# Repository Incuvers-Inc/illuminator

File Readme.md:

# Illuminator
LED Matrix illuminator for IRIS. Because, as any photographer will say, "good lighting is always needed to take a good picture."

## Hardware
- resistor network (one resistor per LED, 256 in total)
- 32x 74HC595 (for 256 outputs total)
- a dimming transistor for the fluorescence LED (5V PWM)
- a trigger transistor for the fluorescence LED (3.3V logic)
- a logic level shifter (four 3.3V -> 5V)
- capacitors to reduce kicks in current draw

### Power
The main power source will be used for the both illumination modules (matrix+ fluorescence LED). This can potentially blow the fuse is all of the components happen to be active at the same time. Luckily there is no requirement for them to simultaneously be active. The lighting flash is much shorter than the timescales for the environmental controls, so the latter can be disabled for the duration of the lighting flash. This must however be controlled by the software. Failure to account for this may result in a blown fuse.

### LED matrix
The fluorescence LED must first be disabled before the matrix LED is activated.

The LED matrix is driven by `74HC595` shift registers that can holds the state of up to 8 LEDs. The state of all the LED's must be first set before they are globally activated by grounding their shared `output_enable` pin.

#### Dimming
Global dimming is made possible with PWM on the `output_enable` input of the `74HC595`. All only one PWM signal is needed to dim the full matrix.

### Fluorescence LED
All the matrix LEDs must first be disabled before the fluorescence LED is lit.
The on/off state of the fluorescence LED is set from a single transistor.

#### Dimming
Dimming for the fluorescence LED is accomplished using the same PWM signal. In order for the matrix to stay off when the fluorescence LED is enabled, all the individual matrix LEDs must first be disabled.

### RPi interface
The RPi supplies inputs as the common PWM, fluorescence LED trigger, SPI for the matrix (three inputs) and of course a common ground.

Since the matrix is powered at 5V, the logic level (SPI and PWM) has to also be  shifted to 5V.

Since the fluorescence LED is trigger from a transistor, the logic level can stay at 3.3V.

## Software

### Illumination flash

The software must make sure that all the matrix LEDs are set to an `off` state after a pattern is finished flashing.
Iy may be good measure to be redundant and also do this before turning on the fluorescence LED.
The same goes for turning off the fluorescence LED before turning on the matrix.

### Power management

Since the LED's are powered from the main power source,
it is important to limit the total current draw from activated sub-components.
It is the software's responsibility to temporary disable components (heating/fans/valves) that could draw current for the duration of the illumination flash. Since this is rather short, it should cause any environmental noticeable disruptions.

NOTE: the activated camera sensor (and post processing) will also cause a short-lived increase in power demand, consider reactivating the environmental subcomponents only after the image is processed.

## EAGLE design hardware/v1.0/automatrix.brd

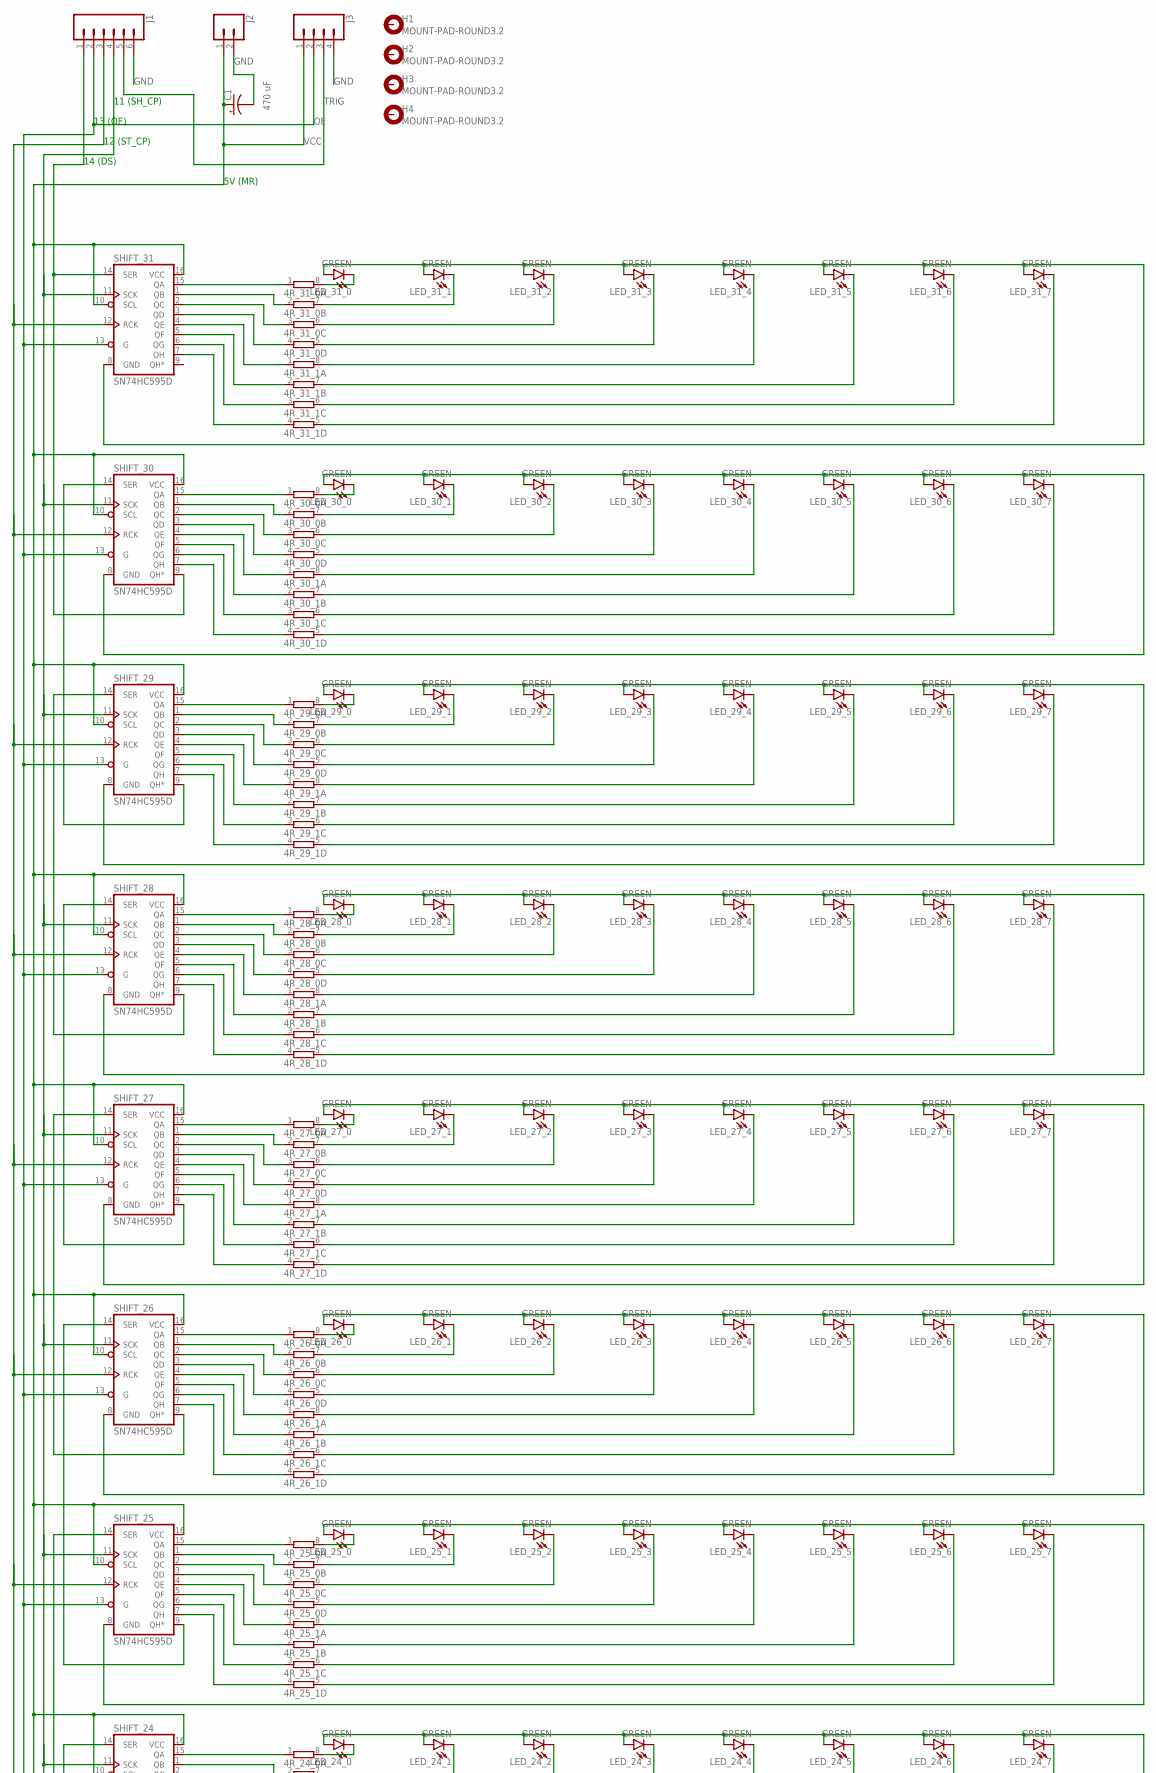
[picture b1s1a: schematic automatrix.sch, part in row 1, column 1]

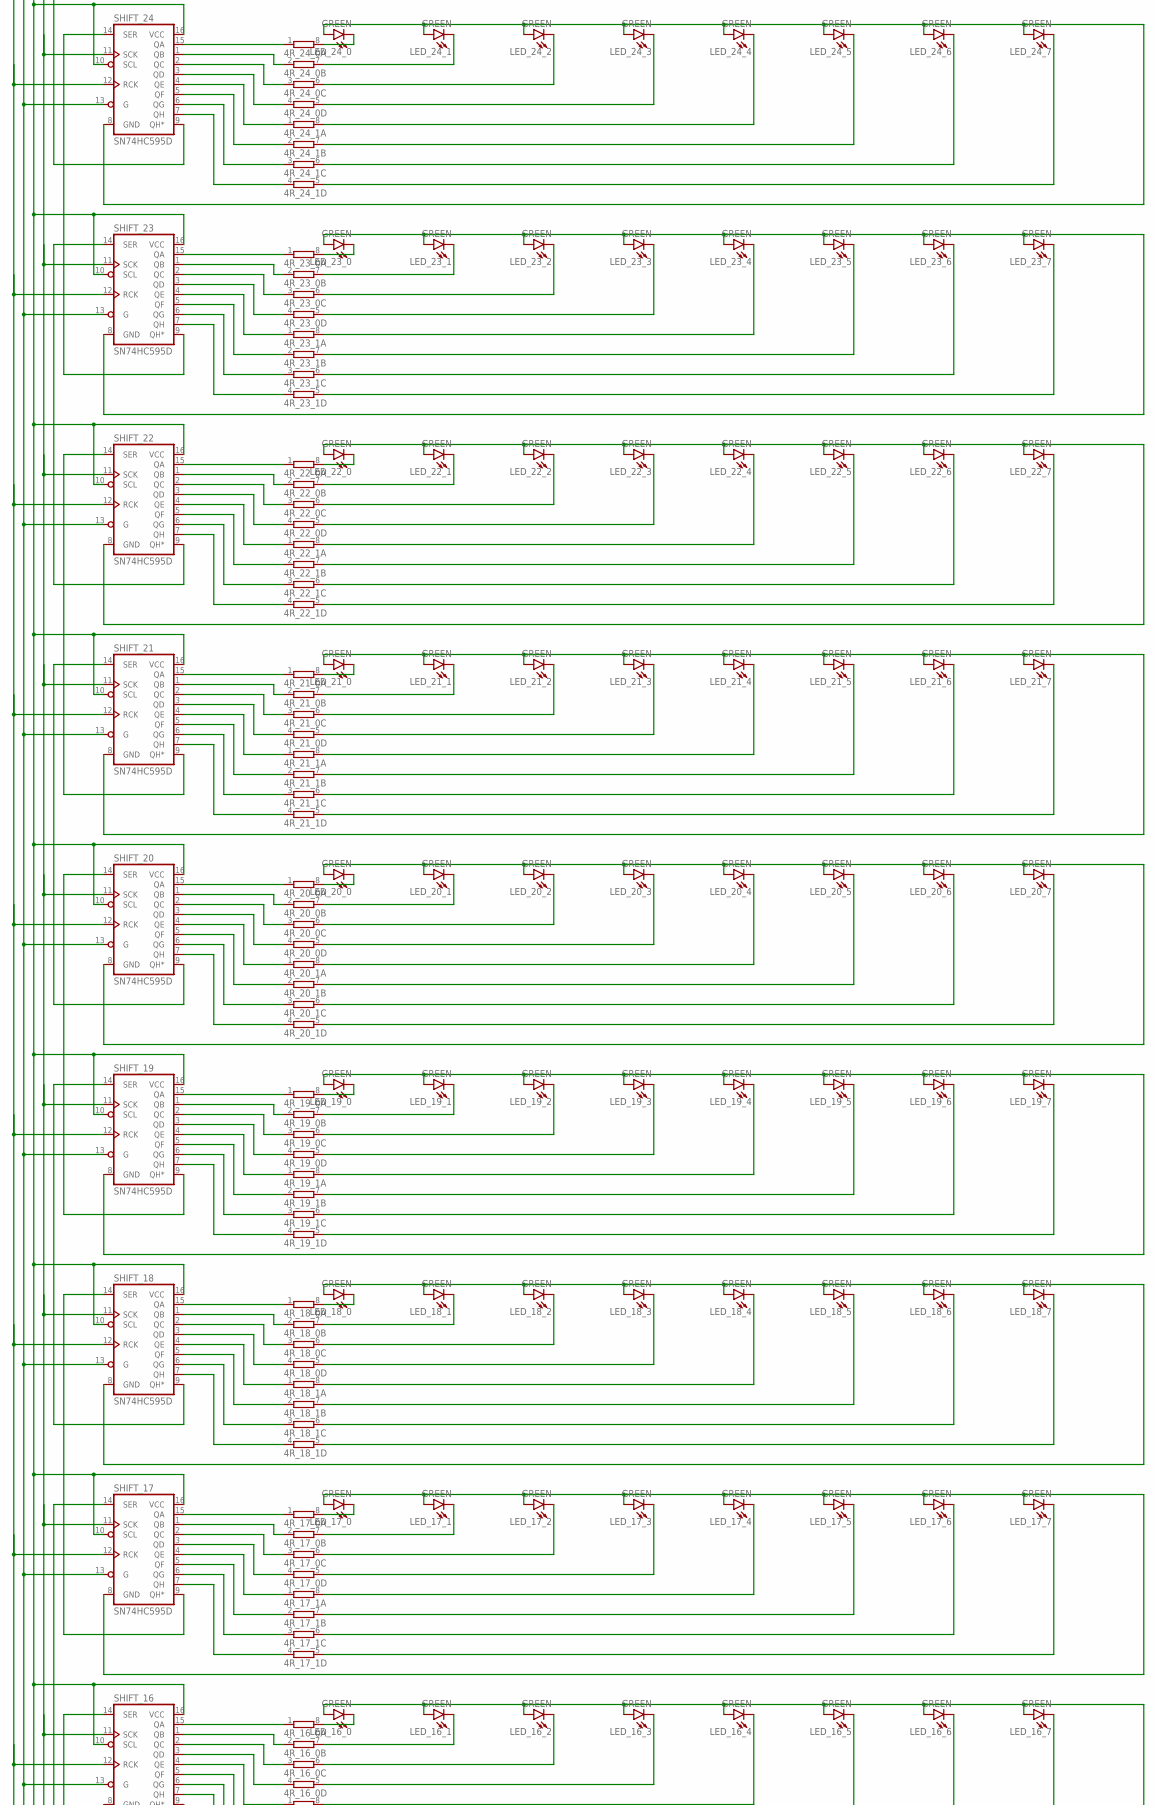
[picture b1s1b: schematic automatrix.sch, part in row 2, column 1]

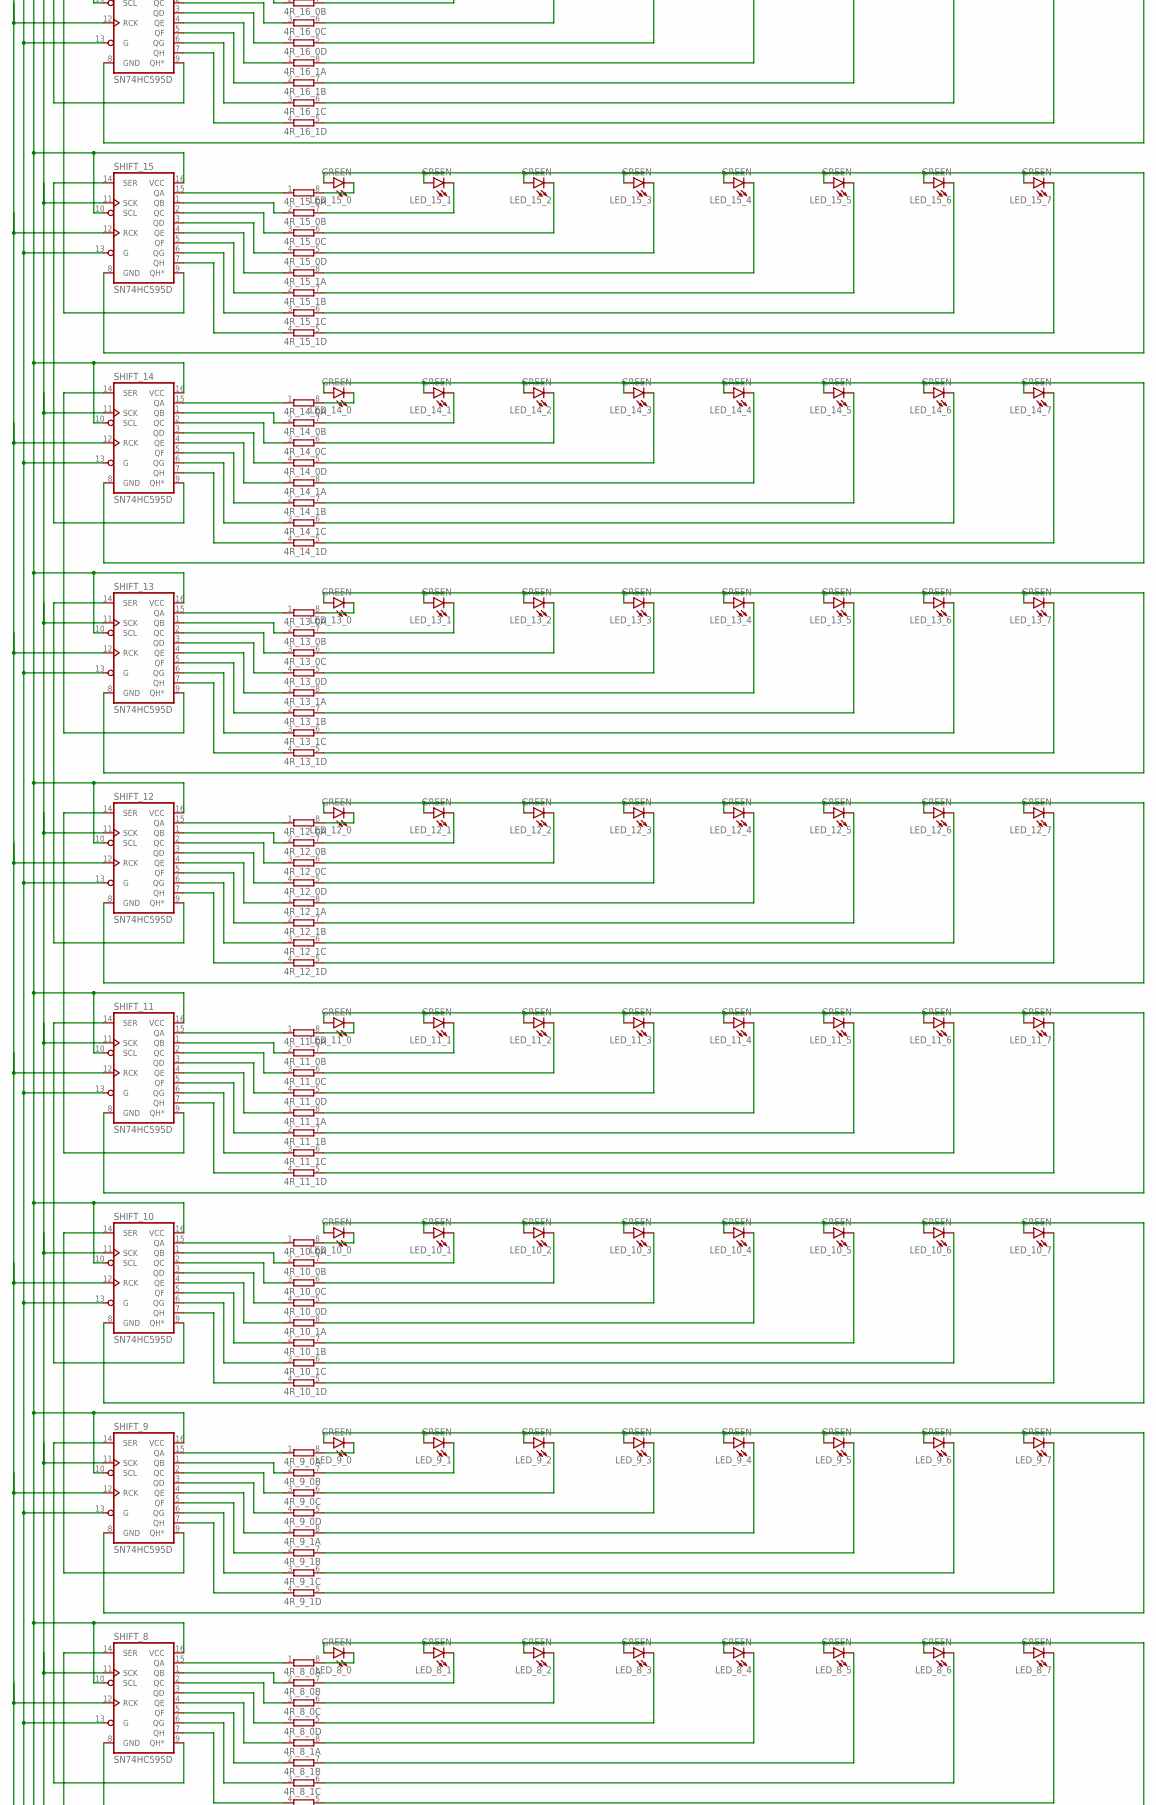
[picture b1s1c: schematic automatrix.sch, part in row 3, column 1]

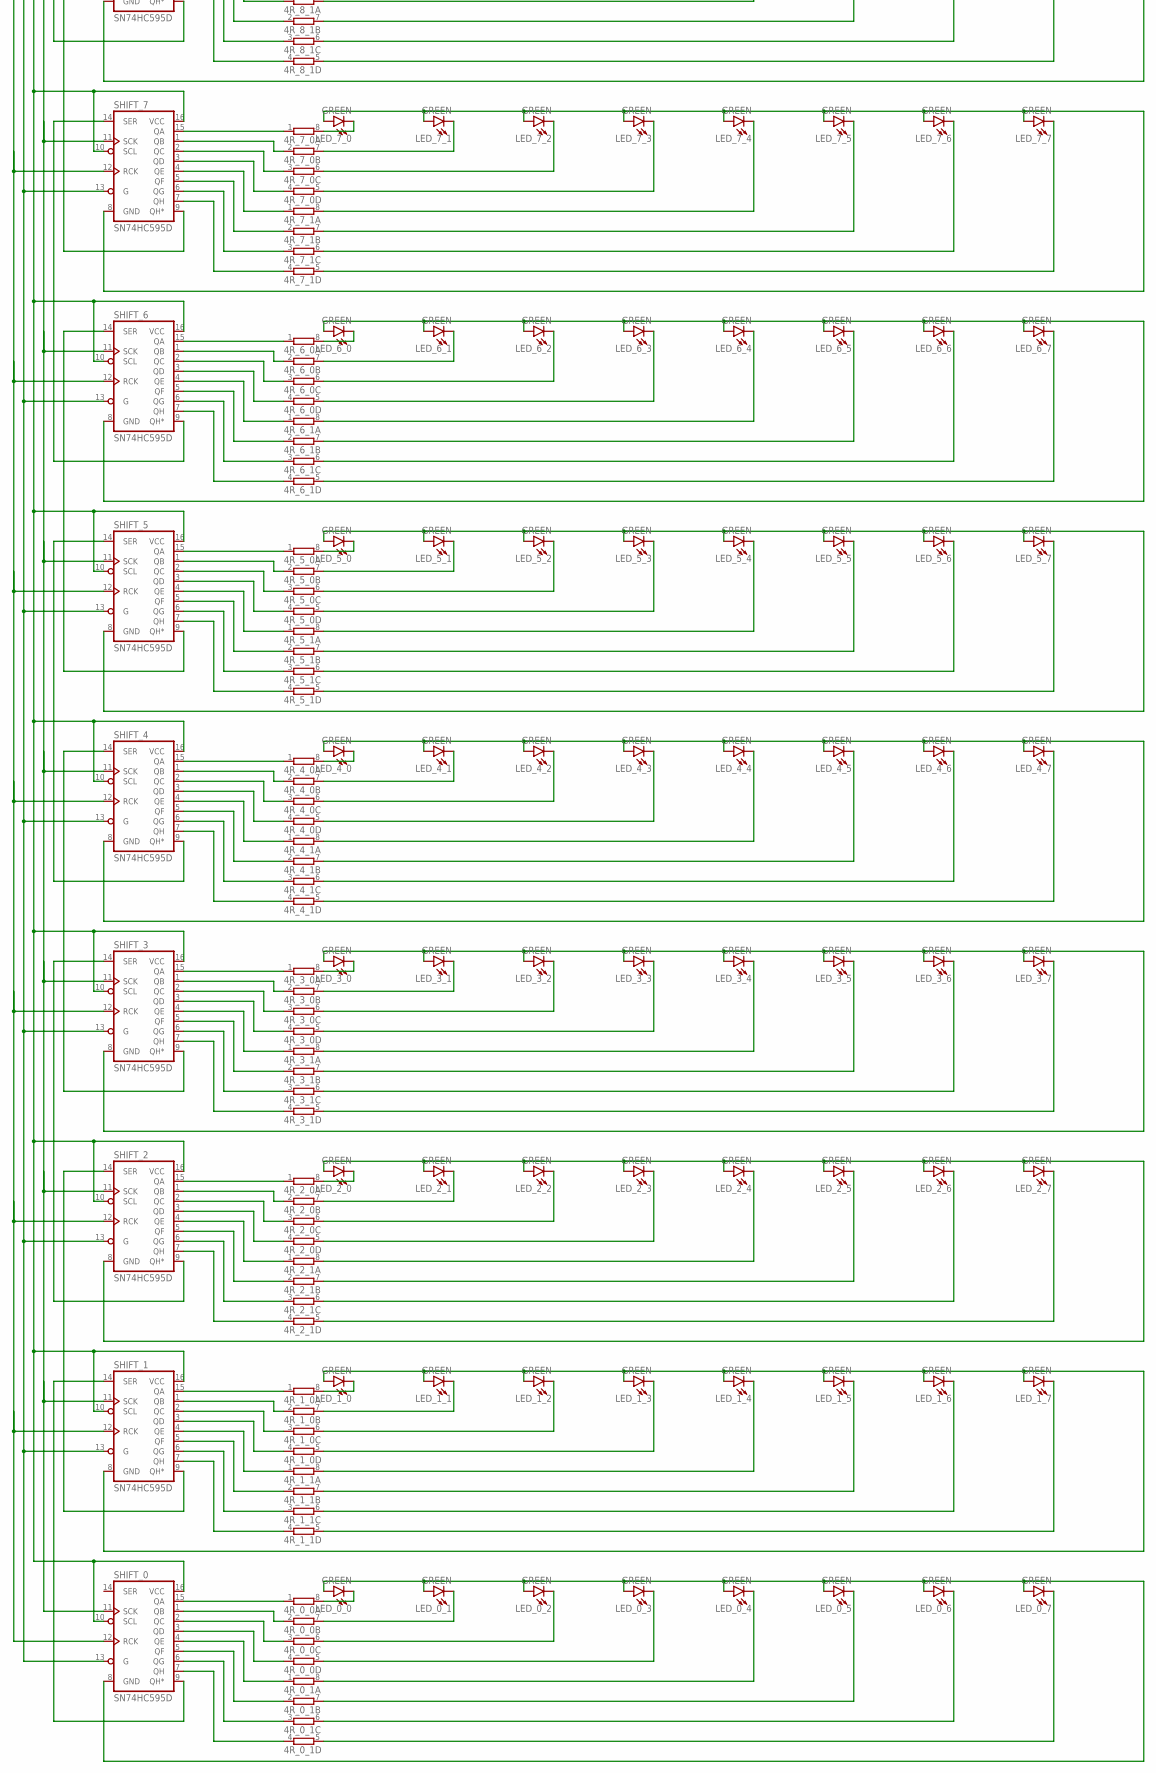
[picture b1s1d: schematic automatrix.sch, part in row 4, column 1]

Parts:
4R_0_0, 4R_0_1, 4R_1_0, 4R_1_1, 4R_2_0, 4R_2_1, 4R_3_0, 4R_3_1, 4R_4_0, 4R_4_1, 4R_5_0, 4R_5_1, 4R_6_0, 4R_6_1, 4R_7_0, 4R_7_1, 4R_8_0, 4R_8_1, 4R_9_0, 4R_9_1, 4R_10_0, 4R_10_1, 4R_11_0, 4R_11_1, 4R_12_0, 4R_12_1, 4R_13_0, 4R_13_1, 4R_14_0, 4R_14_1, 4R_15_0, 4R_15_1, 4R_16_0, 4R_16_1, 4R_17_0, 4R_17_1, 4R_18_0, 4R_18_1, 4R_19_0, 4R_19_1, 4R_20_0, 4R_20_1, 4R_21_0, 4R_21_1, 4R_22_0, 4R_22_1, 4R_23_0, 4R_23_1, 4R_24_0, 4R_24_1, 4R_25_0, 4R_25_1, 4R_26_0, 4R_26_1, 4R_27_0, 4R_27_1, 4R_28_0, 4R_28_1, 4R_29_0, 4R_29_1, 4R_30_0, 4R_30_1, 4R_31_0, 4R_31_1: 4R-N0603-ARC; 0603-ARC
C1: 470 uF; CPOL-RADIAL-5MM-10MM
H1, H2, H3, H4: MOUNT-PAD-ROUND3.2; 3,2-PAD
J1: CONN_06NO_SILK_FEMALE_PTH; 1X06_NO_SILK
J2: CONN_021X02_NO_SILK; 1X02_NO_SILK
J3: CONN_041X04_NO_SILK; 1X04_NO_SILK
LED_0_0, LED_0_1, LED_0_2, LED_0_3, LED_0_4, LED_0_5, LED_0_6, LED_0_7, LED_1_0, LED_1_1, LED_1_2, LED_1_3, LED_1_4, LED_1_5, LED_1_6, LED_1_7, LED_2_0, LED_2_1, LED_2_2, LED_2_3, LED_2_4, LED_2_5, LED_2_6, LED_2_7, LED_3_0, LED_3_1, LED_3_2, LED_3_3, LED_3_4, LED_3_5, LED_3_6, LED_3_7, LED_4_0, LED_4_1, LED_4_2, LED_4_3, LED_4_4, LED_4_5, LED_4_6, LED_4_7, LED_5_0, LED_5_1, LED_5_2, LED_5_3, LED_5_4, LED_5_5, LED_5_6, LED_5_7, LED_6_0, LED_6_1, LED_6_2, LED_6_3, LED_6_4, LED_6_5, LED_6_6, LED_6_7, LED_7_0, LED_7_1, LED_7_2, LED_7_3, LED_7_4, LED_7_5, LED_7_6, LED_7_7, LED_8_0, LED_8_1, LED_8_2, LED_8_3, LED_8_4, LED_8_5, LED_8_6, LED_8_7, LED_9_0, LED_9_1, LED_9_2, LED_9_3, LED_9_4, LED_9_5, LED_9_6, LED_9_7, LED_10_0, LED_10_1, LED_10_2, LED_10_3, LED_10_4, LED_10_5, LED_10_6, LED_10_7, LED_11_0, LED_11_1, LED_11_2, LED_11_3, LED_11_4, LED_11_5, LED_11_6, LED_11_7, LED_12_0, LED_12_1, LED_12_2, LED_12_3, LED_12_4, LED_12_5, LED_12_6, LED_12_7, LED_13_0, LED_13_1, LED_13_2, LED_13_3, LED_13_4, LED_13_5, LED_13_6, LED_13_7, LED_14_0, LED_14_1, LED_14_2, LED_14_3, LED_14_4, LED_14_5, LED_14_6, LED_14_7, LED_15_0, LED_15_1, LED_15_2, LED_15_3, LED_15_4, LED_15_5, LED_15_6, LED_15_7, LED_16_0, LED_16_1, LED_16_2, LED_16_3, LED_16_4, LED_16_5, LED_16_6, LED_16_7, LED_17_0, LED_17_1, LED_17_2, LED_17_3, LED_17_4, LED_17_5, LED_17_6, LED_17_7, LED_18_0, LED_18_1, LED_18_2, LED_18_3, LED_18_4, LED_18_5, LED_18_6, LED_18_7, LED_19_0, LED_19_1, LED_19_2, LED_19_3, LED_19_4, LED_19_5, LED_19_6, LED_19_7, LED_20_0, LED_20_1, LED_20_2, LED_20_3, LED_20_4, LED_20_5, LED_20_6, LED_20_7, LED_21_0, LED_21_1, LED_21_2, LED_21_3, LED_21_4, LED_21_5, LED_21_6, LED_21_7, LED_22_0, LED_22_1, LED_22_2, LED_22_3, LED_22_4, LED_22_5, LED_22_6, LED_22_7, LED_23_0, LED_23_1, LED_23_2, LED_23_3, LED_23_4, LED_23_5, LED_23_6, LED_23_7, LED_24_0, LED_24_1, LED_24_2, LED_24_3, LED_24_4, LED_24_5, LED_24_6, LED_24_7, LED_25_0, LED_25_1, LED_25_2, LED_25_3, LED_25_4, LED_25_5, LED_25_6, LED_25_7, LED_26_0, LED_26_1, LED_26_2, LED_26_3, LED_26_4, LED_26_5, LED_26_6, LED_26_7, LED_27_0, LED_27_1, LED_27_2, LED_27_3, LED_27_4, LED_27_5, LED_27_6, LED_27_7, LED_28_0, LED_28_1, LED_28_2, LED_28_3, LED_28_4, LED_28_5, LED_28_6, LED_28_7, LED_29_0, LED_29_1, LED_29_2, LED_29_3, LED_29_4, LED_29_5, LED_29_6, LED_29_7, LED_30_0, LED_30_1, LED_30_2, LED_30_3, LED_30_4, LED_30_5, LED_30_6, LED_30_7, LED_31_0, LED_31_1, LED_31_2, LED_31_3, LED_31_4, LED_31_5, LED_31_6, LED_31_7: GREEN; LED-0603
SHIFT_0, SHIFT_1, SHIFT_2, SHIFT_3, SHIFT_4, SHIFT_5, SHIFT_6, SHIFT_7, SHIFT_8, SHIFT_9, SHIFT_10, SHIFT_11, SHIFT_12, SHIFT_13, SHIFT_14, SHIFT_15, SHIFT_16, SHIFT_17, SHIFT_18, SHIFT_19, SHIFT_20, SHIFT_21, SHIFT_22, SHIFT_23, SHIFT_24, SHIFT_25, SHIFT_26, SHIFT_27, SHIFT_28, SHIFT_29, SHIFT_30, SHIFT_31: SN74HC595D; SO16

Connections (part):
CLK: J1.4, SHIFT_0.11 (SCK), SHIFT_1.11 (SCK), SHIFT_2.11 (SCK), SHIFT_3.11 (SCK), SHIFT_4.11 (SCK), SHIFT_5.11 (SCK), SHIFT_6.11 (SCK), SHIFT_7.11 (SCK), SHIFT_8.11 (SCK), SHIFT_9.11 (SCK), SHIFT_10.11 (SCK), SHIFT_11.11 (SCK), SHIFT_12.11 (SCK), SHIFT_13.11 (SCK), SHIFT_14.11 (SCK), SHIFT_15.11 (SCK), SHIFT_16.11 (SCK), SHIFT_17.11 (SCK), SHIFT_18.11 (SCK), SHIFT_19.11 (SCK), SHIFT_20.11 (SCK), SHIFT_21.11 (SCK), SHIFT_22.11 (SCK), SHIFT_23.11 (SCK), SHIFT_24.11 (SCK), SHIFT_25.11 (SCK), SHIFT_26.11 (SCK), SHIFT_27.11 (SCK), SHIFT_28.11 (SCK), SHIFT_29.11 (SCK), SHIFT_30.11 (SCK), SHIFT_31.11 (SCK)
GND: C1.-, J1.6, J2.2, J3.4, LED_0_0.A, LED_0_1.A, LED_0_2.A, LED_0_3.A, LED_0_4.A, LED_0_5.A, LED_0_6.A, LED_0_7.A, LED_1_0.A, LED_1_1.A, LED_1_2.A, LED_1_3.A, LED_1_4.A, LED_1_5.A, LED_1_6.A, LED_1_7.A, LED_2_0.A, LED_2_1.A, LED_2_2.A, LED_2_3.A, LED_2_4.A, LED_2_5.A, LED_2_6.A, LED_2_7.A, LED_3_0.A, LED_3_1.A, LED_3_2.A, LED_3_3.A, LED_3_4.A, LED_3_5.A, LED_3_6.A, LED_3_7.A, LED_4_0.A, LED_4_1.A, LED_4_2.A, LED_4_3.A, LED_4_4.A, LED_4_5.A, LED_4_6.A, LED_4_7.A, LED_5_0.A, LED_5_1.A, LED_5_2.A, LED_5_3.A, LED_5_4.A, LED_5_5.A, LED_5_6.A, LED_5_7.A, LED_6_0.A, LED_6_1.A, LED_6_2.A, LED_6_3.A, LED_6_4.A, LED_6_5.A, LED_6_6.A, LED_6_7.A, LED_7_0.A, LED_7_1.A, LED_7_2.A, LED_7_3.A, LED_7_4.A, LED_7_5.A, LED_7_6.A, LED_7_7.A, LED_8_0.A, LED_8_1.A, LED_8_2.A, LED_8_3.A, LED_8_4.A, LED_8_5.A, LED_8_6.A, LED_8_7.A, LED_9_0.A, LED_9_1.A, LED_9_2.A, LED_9_3.A, LED_9_4.A, LED_9_5.A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
OE: J1.2, J3.2, SHIFT_0.13 (G), SHIFT_1.13 (G), SHIFT_2.13 (G), SHIFT_3.13 (G), SHIFT_4.13 (G), SHIFT_5.13 (G), SHIFT_6.13 (G), SHIFT_7.13 (G), SHIFT_8.13 (G), SHIFT_9.13 (G), SHIFT_10.13 (G), SHIFT_11.13 (G), SHIFT_12.13 (G), SHIFT_13.13 (G), SHIFT_14.13 (G), SHIFT_15.13 (G), SHIFT_16.13 (G), SHIFT_17.13 (G), SHIFT_18.13 (G), SHIFT_19.13 (G), SHIFT_20.13 (G), SHIFT_21.13 (G), SHIFT_22.13 (G), SHIFT_23.13 (G), SHIFT_24.13 (G), SHIFT_25.13 (G), SHIFT_26.13 (G), SHIFT_27.13 (G), SHIFT_28.13 (G), SHIFT_29.13 (G), SHIFT_30.13 (G), SHIFT_31.13 (G)
Q0_0: 4R_0_0.1, 4R_0_0.8 (2), LED_0_0.C, SHIFT_0.15 (QA)
Q0_1: 4R_0_0.2 (1), 4R_0_0.7 (2), LED_0_1.C, SHIFT_0.1 (QB)
Q0_2: 4R_0_0.3 (1), 4R_0_0.6 (2), LED_0_2.C, SHIFT_0.2 (QC)
Q0_3: 4R_0_0.4 (1), 4R_0_0.5 (2), LED_0_3.C, SHIFT_0.3 (QD)
Q0_4: 4R_0_1.1, 4R_0_1.8 (2), LED_0_4.C, SHIFT_0.4 (QE)
Q0_5: 4R_0_1.2 (1), 4R_0_1.7 (2), LED_0_5.C, SHIFT_0.5 (QF)
Q0_6: 4R_0_1.3 (1), 4R_0_1.6 (2), LED_0_6.C, SHIFT_0.6 (QG)
Q0_7: 4R_0_1.4 (1), 4R_0_1.5 (2), LED_0_7.C, SHIFT_0.7 (QH)
Q1_0: 4R_1_0.1, 4R_1_0.8 (2), LED_1_0.C, SHIFT_1.15 (QA)
Q1_1: 4R_1_0.2 (1), 4R_1_0.7 (2), LED_1_1.C, SHIFT_1.1 (QB)
Q1_2: 4R_1_0.3 (1), 4R_1_0.6 (2), LED_1_2.C, SHIFT_1.2 (QC)
Q1_3: 4R_1_0.4 (1), 4R_1_0.5 (2), LED_1_3.C, SHIFT_1.3 (QD)
Q1_4: 4R_1_1.1, 4R_1_1.8 (2), LED_1_4.C, SHIFT_1.4 (QE)
Q1_5: 4R_1_1.2 (1), 4R_1_1.7 (2), LED_1_5.C, SHIFT_1.5 (QF)
Q1_6: 4R_1_1.3 (1), 4R_1_1.6 (2), LED_1_6.C, SHIFT_1.6 (QG)
Q1_7: 4R_1_1.4 (1), 4R_1_1.5 (2), LED_1_7.C, SHIFT_1.7 (QH)
Q2_0: 4R_2_0.1, 4R_2_0.8 (2), LED_2_0.C, SHIFT_2.15 (QA)
Q2_1: 4R_2_0.2 (1), 4R_2_0.7 (2), LED_2_1.C, SHIFT_2.1 (QB)
Q2_2: 4R_2_0.3 (1), 4R_2_0.6 (2), LED_2_2.C, SHIFT_2.2 (QC)
Q2_3: 4R_2_0.4 (1), 4R_2_0.5 (2), LED_2_3.C, SHIFT_2.3 (QD)
Q2_4: 4R_2_1.1, 4R_2_1.8 (2), LED_2_4.C, SHIFT_2.4 (QE)
Q2_5: 4R_2_1.2 (1), 4R_2_1.7 (2), LED_2_5.C, SHIFT_2.5 (QF)
Q2_6: 4R_2_1.3 (1), 4R_2_1.6 (2), LED_2_6.C, SHIFT_2.6 (QG)
Q2_7: 4R_2_1.4 (1), 4R_2_1.5 (2), LED_2_7.C, SHIFT_2.7 (QH)
Q3_0: 4R_3_0.1, 4R_3_0.8 (2), LED_3_0.C, SHIFT_3.15 (QA)
Q3_1: 4R_3_0.2 (1), 4R_3_0.7 (2), LED_3_1.C, SHIFT_3.1 (QB)
Q3_2: 4R_3_0.3 (1), 4R_3_0.6 (2), LED_3_2.C, SHIFT_3.2 (QC)
Q3_3: 4R_3_0.4 (1), 4R_3_0.5 (2), LED_3_3.C, SHIFT_3.3 (QD)
Q3_4: 4R_3_1.1, 4R_3_1.8 (2), LED_3_4.C, SHIFT_3.4 (QE)
Q3_5: 4R_3_1.2 (1), 4R_3_1.7 (2), LED_3_5.C, SHIFT_3.5 (QF)
Q3_6: 4R_3_1.3 (1), 4R_3_1.6 (2), LED_3_6.C, SHIFT_3.6 (QG)
Q3_7: 4R_3_1.4 (1), 4R_3_1.5 (2), LED_3_7.C, SHIFT_3.7 (QH)
Q4_0: 4R_4_0.1, 4R_4_0.8 (2), LED_4_0.C, SHIFT_4.15 (QA)
Q4_1: 4R_4_0.2 (1), 4R_4_0.7 (2), LED_4_1.C, SHIFT_4.1 (QB)
Q4_2: 4R_4_0.3 (1), 4R_4_0.6 (2), LED_4_2.C, SHIFT_4.2 (QC)
Q4_3: 4R_4_0.4 (1), 4R_4_0.5 (2), LED_4_3.C, SHIFT_4.3 (QD)
Q4_4: 4R_4_1.1, 4R_4_1.8 (2), LED_4_4.C, SHIFT_4.4 (QE)
Q4_5: 4R_4_1.2 (1), 4R_4_1.7 (2), LED_4_5.C, SHIFT_4.5 (QF)
Q4_6: 4R_4_1.3 (1), 4R_4_1.6 (2), LED_4_6.C, SHIFT_4.6 (QG)
Q4_7: 4R_4_1.4 (1), 4R_4_1.5 (2), LED_4_7.C, SHIFT_4.7 (QH)
Q5_0: 4R_5_0.1, 4R_5_0.8 (2), LED_5_0.C, SHIFT_5.15 (QA)
Q5_1: 4R_5_0.2 (1), 4R_5_0.7 (2), LED_5_1.C, SHIFT_5.1 (QB)
Q5_2: 4R_5_0.3 (1), 4R_5_0.6 (2), LED_5_2.C, SHIFT_5.2 (QC)
Q5_3: 4R_5_0.4 (1), 4R_5_0.5 (2), LED_5_3.C, SHIFT_5.3 (QD)
Q5_4: 4R_5_1.1, 4R_5_1.8 (2), LED_5_4.C, SHIFT_5.4 (QE)
Q5_5: 4R_5_1.2 (1), 4R_5_1.7 (2), LED_5_5.C, SHIFT_5.5 (QF)
Q5_6: 4R_5_1.3 (1), 4R_5_1.6 (2), LED_5_6.C, SHIFT_5.6 (QG)
Q5_7: 4R_5_1.4 (1), 4R_5_1.5 (2), LED_5_7.C, SHIFT_5.7 (QH)
Q6_0: 4R_6_0.1, 4R_6_0.8 (2), LED_6_0.C, SHIFT_6.15 (QA)
Q6_1: 4R_6_0.2 (1), 4R_6_0.7 (2), LED_6_1.C, SHIFT_6.1 (QB)
Q6_2: 4R_6_0.3 (1), 4R_6_0.6 (2), LED_6_2.C, SHIFT_6.2 (QC)
Q6_3: 4R_6_0.4 (1), 4R_6_0.5 (2), LED_6_3.C, SHIFT_6.3 (QD)
Q6_4: 4R_6_1.1, 4R_6_1.8 (2), LED_6_4.C, SHIFT_6.4 (QE)
Q6_5: 4R_6_1.2 (1), 4R_6_1.7 (2), LED_6_5.C, SHIFT_6.5 (QF)
Q6_6: 4R_6_1.3 (1), 4R_6_1.6 (2), LED_6_6.C, SHIFT_6.6 (QG)
Q6_7: 4R_6_1.4 (1), 4R_6_1.5 (2), LED_6_7.C, SHIFT_6.7 (QH)
Q7_0: 4R_7_0.1, 4R_7_0.8 (2), LED_7_0.C, SHIFT_7.15 (QA)
Q7_1: 4R_7_0.2 (1), 4R_7_0.7 (2), LED_7_1.C, SHIFT_7.1 (QB)
Q7_2: 4R_7_0.3 (1), 4R_7_0.6 (2), LED_7_2.C, SHIFT_7.2 (QC)
Q7_3: 4R_7_0.4 (1), 4R_7_0.5 (2), LED_7_3.C, SHIFT_7.3 (QD)
Q7_4: 4R_7_1.1, 4R_7_1.8 (2), LED_7_4.C, SHIFT_7.4 (QE)
Q7_5: 4R_7_1.2 (1), 4R_7_1.7 (2), LED_7_5.C, SHIFT_7.5 (QF)
Q7_6: 4R_7_1.3 (1), 4R_7_1.6 (2), LED_7_6.C, SHIFT_7.6 (QG)
Q7_7: 4R_7_1.4 (1), 4R_7_1.5 (2), LED_7_7.C, SHIFT_7.7 (QH)
Q8_0: 4R_8_0.1, 4R_8_0.8 (2), LED_8_0.C, SHIFT_8.15 (QA)
Q8_1: 4R_8_0.2 (1), 4R_8_0.7 (2), LED_8_1.C, SHIFT_8.1 (QB)
Q8_2: 4R_8_0.3 (1), 4R_8_0.6 (2), LED_8_2.C, SHIFT_8.2 (QC)
Q8_3: 4R_8_0.4 (1), 4R_8_0.5 (2), LED_8_3.C, SHIFT_8.3 (QD)
Q8_4: 4R_8_1.1, 4R_8_1.8 (2), LED_8_4.C, SHIFT_8.4 (QE)
Q8_5: 4R_8_1.2 (1), 4R_8_1.7 (2), LED_8_5.C, SHIFT_8.5 (QF)
Q8_6: 4R_8_1.3 (1), 4R_8_1.6 (2), LED_8_6.C, SHIFT_8.6 (QG)
Q8_7: 4R_8_1.4 (1), 4R_8_1.5 (2), LED_8_7.C, SHIFT_8.7 (QH)
Q9_0: 4R_9_0.1, 4R_9_0.8 (2), LED_9_0.C, SHIFT_9.15 (QA)
Q9_1: 4R_9_0.2 (1), 4R_9_0.7 (2), LED_9_1.C, SHIFT_9.1 (QB)
Q9_2: 4R_9_0.3 (1), 4R_9_0.6 (2), LED_9_2.C, SHIFT_9.2 (QC)
Q9_3: 4R_9_0.4 (1), 4R_9_0.5 (2), LED_9_3.C, SHIFT_9.3 (QD)
Q9_4: 4R_9_1.1, 4R_9_1.8 (2), LED_9_4.C, SHIFT_9.4 (QE)
Q9_5: 4R_9_1.2 (1), 4R_9_1.7 (2), LED_9_5.C, SHIFT_9.5 (QF)
Q9_6: 4R_9_1.3 (1), 4R_9_1.6 (2), LED_9_6.C, SHIFT_9.6 (QG)
Q9_7: 4R_9_1.4 (1), 4R_9_1.5 (2), LED_9_7.C, SHIFT_9.7 (QH)
Q10_0: 4R_10_0.1, 4R_10_0.8 (2), LED_10_0.C, SHIFT_10.15 (QA)
Q10_1: 4R_10_0.2 (1), 4R_10_0.7 (2), LED_10_1.C, SHIFT_10.1 (QB)
Q10_2: 4R_10_0.3 (1), 4R_10_0.6 (2), LED_10_2.C, SHIFT_10.2 (QC)
Q10_3: 4R_10_0.4 (1), 4R_10_0.5 (2), LED_10_3.C, SHIFT_10.3 (QD)
Q10_4: 4R_10_1.1, 4R_10_1.8 (2), LED_10_4.C, SHIFT_10.4 (QE)
Q10_5: 4R_10_1.2 (1), 4R_10_1.7 (2), LED_10_5.C, SHIFT_10.5 (QF)
Q10_6: 4R_10_1.3 (1), 4R_10_1.6 (2), LED_10_6.C, SHIFT_10.6 (QG)
Q10_7: 4R_10_1.4 (1), 4R_10_1.5 (2), LED_10_7.C, SHIFT_10.7 (QH)
Q11_0: 4R_11_0.1, 4R_11_0.8 (2), LED_11_0.C, SHIFT_11.15 (QA)
Q11_1: 4R_11_0.2 (1), 4R_11_0.7 (2), LED_11_1.C, SHIFT_11.1 (QB)
Q11_2: 4R_11_0.3 (1), 4R_11_0.6 (2), LED_11_2.C, SHIFT_11.2 (QC)
Q11_3: 4R_11_0.4 (1), 4R_11_0.5 (2), LED_11_3.C, SHIFT_11.3 (QD)
Q11_4: 4R_11_1.1, 4R_11_1.8 (2), LED_11_4.C, SHIFT_11.4 (QE)
Q11_5: 4R_11_1.2 (1), 4R_11_1.7 (2), LED_11_5.C, SHIFT_11.5 (QF)
Q11_6: 4R_11_1.3 (1), 4R_11_1.6 (2), LED_11_6.C, SHIFT_11.6 (QG)
Q11_7: 4R_11_1.4 (1), 4R_11_1.5 (2), LED_11_7.C, SHIFT_11.7 (QH)
Q12_0: 4R_12_0.1, 4R_12_0.8 (2), LED_12_0.C, SHIFT_12.15 (QA)
Q12_1: 4R_12_0.2 (1), 4R_12_0.7 (2), LED_12_1.C, SHIFT_12.1 (QB)
Q12_2: 4R_12_0.3 (1), 4R_12_0.6 (2), LED_12_2.C, SHIFT_12.2 (QC)
Q12_3: 4R_12_0.4 (1), 4R_12_0.5 (2), LED_12_3.C, SHIFT_12.3 (QD)
Q12_4: 4R_12_1.1, 4R_12_1.8 (2), LED_12_4.C, SHIFT_12.4 (QE)
Q12_5: 4R_12_1.2 (1), 4R_12_1.7 (2), LED_12_5.C, SHIFT_12.5 (QF)
Q12_6: 4R_12_1.3 (1), 4R_12_1.6 (2), LED_12_6.C, SHIFT_12.6 (QG)
Q12_7: 4R_12_1.4 (1), 4R_12_1.5 (2), LED_12_7.C, SHIFT_12.7 (QH)
Q13_0: 4R_13_0.1, 4R_13_0.8 (2), LED_13_0.C, SHIFT_13.15 (QA)
Q13_1: 4R_13_0.2 (1), 4R_13_0.7 (2), LED_13_1.C, SHIFT_13.1 (QB)
Q13_2: 4R_13_0.3 (1), 4R_13_0.6 (2), LED_13_2.C, SHIFT_13.2 (QC)
Q13_3: 4R_13_0.4 (1), 4R_13_0.5 (2), LED_13_3.C, SHIFT_13.3 (QD)
Q13_4: 4R_13_1.1, 4R_13_1.8 (2), LED_13_4.C, SHIFT_13.4 (QE)
Q13_5: 4R_13_1.2 (1), 4R_13_1.7 (2), LED_13_5.C, SHIFT_13.5 (QF)
Q13_6: 4R_13_1.3 (1), 4R_13_1.6 (2), LED_13_6.C, SHIFT_13.6 (QG)
Q13_7: 4R_13_1.4 (1), 4R_13_1.5 (2), LED_13_7.C, SHIFT_13.7 (QH)
Q14_0: 4R_14_0.1, 4R_14_0.8 (2), LED_14_0.C, SHIFT_14.15 (QA)
Q14_1: 4R_14_0.2 (1), 4R_14_0.7 (2), LED_14_1.C, SHIFT_14.1 (QB)
Q14_2: 4R_14_0.3 (1), 4R_14_0.6 (2), LED_14_2.C, SHIFT_14.2 (QC)
Q14_3: 4R_14_0.4 (1), 4R_14_0.5 (2), LED_14_3.C, SHIFT_14.3 (QD)
Q14_4: 4R_14_1.1, 4R_14_1.8 (2), LED_14_4.C, SHIFT_14.4 (QE)
Q14_5: 4R_14_1.2 (1), 4R_14_1.7 (2), LED_14_5.C, SHIFT_14.5 (QF)
Q14_6: 4R_14_1.3 (1), 4R_14_1.6 (2), LED_14_6.C, SHIFT_14.6 (QG)
Q14_7: 4R_14_1.4 (1), 4R_14_1.5 (2), LED_14_7.C, SHIFT_14.7 (QH)
Q15_0: 4R_15_0.1, 4R_15_0.8 (2), LED_15_0.C, SHIFT_15.15 (QA)
Q15_1: 4R_15_0.2 (1), 4R_15_0.7 (2), LED_15_1.C, SHIFT_15.1 (QB)
Q15_2: 4R_15_0.3 (1), 4R_15_0.6 (2), LED_15_2.C, SHIFT_15.2 (QC)
Q15_3: 4R_15_0.4 (1), 4R_15_0.5 (2), LED_15_3.C, SHIFT_15.3 (QD)
Q15_4: 4R_15_1.1, 4R_15_1.8 (2), LED_15_4.C, SHIFT_15.4 (QE)
Q15_5: 4R_15_1.2 (1), 4R_15_1.7 (2), LED_15_5.C, SHIFT_15.5 (QF)
Q15_6: 4R_15_1.3 (1), 4R_15_1.6 (2), LED_15_6.C, SHIFT_15.6 (QG)
Q15_7: 4R_15_1.4 (1), 4R_15_1.5 (2), LED_15_7.C, SHIFT_15.7 (QH)
Q16_0: 4R_16_0.1, 4R_16_0.8 (2), LED_16_0.C, SHIFT_16.15 (QA)
Q16_1: 4R_16_0.2 (1), 4R_16_0.7 (2), LED_16_1.C, SHIFT_16.1 (QB)
Q16_2: 4R_16_0.3 (1), 4R_16_0.6 (2), LED_16_2.C, SHIFT_16.2 (QC)
Q16_3: 4R_16_0.4 (1), 4R_16_0.5 (2), LED_16_3.C, SHIFT_16.3 (QD)
Q16_4: 4R_16_1.1, 4R_16_1.8 (2), LED_16_4.C, SHIFT_16.4 (QE)
Q16_5: 4R_16_1.2 (1), 4R_16_1.7 (2), LED_16_5.C, SHIFT_16.5 (QF)
Q16_6: 4R_16_1.3 (1), 4R_16_1.6 (2), LED_16_6.C, SHIFT_16.6 (QG)
Q16_7: 4R_16_1.4 (1), 4R_16_1.5 (2), LED_16_7.C, SHIFT_16.7 (QH)
Q17_0: 4R_17_0.1, 4R_17_0.8 (2), LED_17_0.C, SHIFT_17.15 (QA)
Q17_1: 4R_17_0.2 (1), 4R_17_0.7 (2), LED_17_1.C, SHIFT_17.1 (QB)
Q17_2: 4R_17_0.3 (1), 4R_17_0.6 (2), LED_17_2.C, SHIFT_17.2 (QC)
Q17_3: 4R_17_0.4 (1), 4R_17_0.5 (2), LED_17_3.C, SHIFT_17.3 (QD)
Q17_4: 4R_17_1.1, 4R_17_1.8 (2), LED_17_4.C, SHIFT_17.4 (QE)
Q17_5: 4R_17_1.2 (1), 4R_17_1.7 (2), LED_17_5.C, SHIFT_17.5 (QF)
Q17_6: 4R_17_1.3 (1), 4R_17_1.6 (2), LED_17_6.C, SHIFT_17.6 (QG)
Q17_7: 4R_17_1.4 (1), 4R_17_1.5 (2), LED_17_7.C, SHIFT_17.7 (QH)
Q18_0: 4R_18_0.1, 4R_18_0.8 (2), LED_18_0.C, SHIFT_18.15 (QA)
Q18_1: 4R_18_0.2 (1), 4R_18_0.7 (2), LED_18_1.C, SHIFT_18.1 (QB)
Q18_2: 4R_18_0.3 (1), 4R_18_0.6 (2), LED_18_2.C, SHIFT_18.2 (QC)
Q18_3: 4R_18_0.4 (1), 4R_18_0.5 (2), LED_18_3.C, SHIFT_18.3 (QD)
Q18_4: 4R_18_1.1, 4R_18_1.8 (2), LED_18_4.C, SHIFT_18.4 (QE)
Q18_5: 4R_18_1.2 (1), 4R_18_1.7 (2), LED_18_5.C, SHIFT_18.5 (QF)
Q18_6: 4R_18_1.3 (1), 4R_18_1.6 (2), LED_18_6.C, SHIFT_18.6 (QG)
Q18_7: 4R_18_1.4 (1), 4R_18_1.5 (2), LED_18_7.C, SHIFT_18.7 (QH)
Q19_0: 4R_19_0.1, 4R_19_0.8 (2), LED_19_0.C, SHIFT_19.15 (QA)
Q19_1: 4R_19_0.2 (1), 4R_19_0.7 (2), LED_19_1.C, SHIFT_19.1 (QB)
Q19_2: 4R_19_0.3 (1), 4R_19_0.6 (2), LED_19_2.C, SHIFT_19.2 (QC)
Q19_3: 4R_19_0.4 (1), 4R_19_0.5 (2), LED_19_3.C, SHIFT_19.3 (QD)
Q19_4: 4R_19_1.1, 4R_19_1.8 (2), LED_19_4.C, SHIFT_19.4 (QE)
Q19_5: 4R_19_1.2 (1), 4R_19_1.7 (2), LED_19_5.C, SHIFT_19.5 (QF)
Q19_6: 4R_19_1.3 (1), 4R_19_1.6 (2), LED_19_6.C, SHIFT_19.6 (QG)
Q19_7: 4R_19_1.4 (1), 4R_19_1.5 (2), LED_19_7.C, SHIFT_19.7 (QH)
Q20_0: 4R_20_0.1, 4R_20_0.8 (2), LED_20_0.C, SHIFT_20.15 (QA)
Q20_1: 4R_20_0.2 (1), 4R_20_0.7 (2), LED_20_1.C, SHIFT_20.1 (QB)
Q20_2: 4R_20_0.3 (1), 4R_20_0.6 (2), LED_20_2.C, SHIFT_20.2 (QC)
Q20_3: 4R_20_0.4 (1), 4R_20_0.5 (2), LED_20_3.C, SHIFT_20.3 (QD)
Q20_4: 4R_20_1.1, 4R_20_1.8 (2), LED_20_4.C, SHIFT_20.4 (QE)
Q20_5: 4R_20_1.2 (1), 4R_20_1.7 (2), LED_20_5.C, SHIFT_20.5 (QF)
Q20_6: 4R_20_1.3 (1), 4R_20_1.6 (2), LED_20_6.C, SHIFT_20.6 (QG)
Q20_7: 4R_20_1.4 (1), 4R_20_1.5 (2), LED_20_7.C, SHIFT_20.7 (QH)
Q21_0: 4R_21_0.1, 4R_21_0.8 (2), LED_21_0.C, SHIFT_21.15 (QA)
Q21_1: 4R_21_0.2 (1), 4R_21_0.7 (2), LED_21_1.C, SHIFT_21.1 (QB)
Q21_2: 4R_21_0.3 (1), 4R_21_0.6 (2), LED_21_2.C, SHIFT_21.2 (QC)
Q21_3: 4R_21_0.4 (1), 4R_21_0.5 (2), LED_21_3.C, SHIFT_21.3 (QD)
Q21_4: 4R_21_1.1, 4R_21_1.8 (2), LED_21_4.C, SHIFT_21.4 (QE)
Q21_5: 4R_21_1.2 (1), 4R_21_1.7 (2), LED_21_5.C, SHIFT_21.5 (QF)
Q21_6: 4R_21_1.3 (1), 4R_21_1.6 (2), LED_21_6.C, SHIFT_21.6 (QG)
Q21_7: 4R_21_1.4 (1), 4R_21_1.5 (2), LED_21_7.C, SHIFT_21.7 (QH)
Q22_0: 4R_22_0.1, 4R_22_0.8 (2), LED_22_0.C, SHIFT_22.15 (QA)
Q22_1: 4R_22_0.2 (1), 4R_22_0.7 (2), LED_22_1.C, SHIFT_22.1 (QB)
Q22_2: 4R_22_0.3 (1), 4R_22_0.6 (2), LED_22_2.C, SHIFT_22.2 (QC)
Q22_3: 4R_22_0.4 (1), 4R_22_0.5 (2), LED_22_3.C, SHIFT_22.3 (QD)
Q22_4: 4R_22_1.1, 4R_22_1.8 (2), LED_22_4.C, SHIFT_22.4 (QE)
Q22_5: 4R_22_1.2 (1), 4R_22_1.7 (2), LED_22_5.C, SHIFT_22.5 (QF)
Q22_6: 4R_22_1.3 (1), 4R_22_1.6 (2), LED_22_6.C, SHIFT_22.6 (QG)
Q22_7: 4R_22_1.4 (1), 4R_22_1.5 (2), LED_22_7.C, SHIFT_22.7 (QH)
Q23_0: 4R_23_0.1, 4R_23_0.8 (2), LED_23_0.C, SHIFT_23.15 (QA)
Q23_1: 4R_23_0.2 (1), 4R_23_0.7 (2), LED_23_1.C, SHIFT_23.1 (QB)
Q23_2: 4R_23_0.3 (1), 4R_23_0.6 (2), LED_23_2.C, SHIFT_23.2 (QC)
Q23_3: 4R_23_0.4 (1), 4R_23_0.5 (2), LED_23_3.C, SHIFT_23.3 (QD)
Q23_4: 4R_23_1.1, 4R_23_1.8 (2), LED_23_4.C, SHIFT_23.4 (QE)
Q23_5: 4R_23_1.2 (1), 4R_23_1.7 (2), LED_23_5.C, SHIFT_23.5 (QF)
Q23_6: 4R_23_1.3 (1), 4R_23_1.6 (2), LED_23_6.C, SHIFT_23.6 (QG)
Q23_7: 4R_23_1.4 (1), 4R_23_1.5 (2), LED_23_7.C, SHIFT_23.7 (QH)
Q24_0: 4R_24_0.1, 4R_24_0.8 (2), LED_24_0.C, SHIFT_24.15 (QA)
Q24_1: 4R_24_0.2 (1), 4R_24_0.7 (2), LED_24_1.C, SHIFT_24.1 (QB)
Q24_2: 4R_24_0.3 (1), 4R_24_0.6 (2), LED_24_2.C, SHIFT_24.2 (QC)
Q24_3: 4R_24_0.4 (1), 4R_24_0.5 (2), LED_24_3.C, SHIFT_24.3 (QD)
Q24_4: 4R_24_1.1, 4R_24_1.8 (2), LED_24_4.C, SHIFT_24.4 (QE)
Q24_5: 4R_24_1.2 (1), 4R_24_1.7 (2), LED_24_5.C, SHIFT_24.5 (QF)
Q24_6: 4R_24_1.3 (1), 4R_24_1.6 (2), LED_24_6.C, SHIFT_24.6 (QG)
Q24_7: 4R_24_1.4 (1), 4R_24_1.5 (2), LED_24_7.C, SHIFT_24.7 (QH)
Q25_0: 4R_25_0.1, 4R_25_0.8 (2), LED_25_0.C, SHIFT_25.15 (QA)
Q25_1: 4R_25_0.2 (1), 4R_25_0.7 (2), LED_25_1.C, SHIFT_25.1 (QB)
Q25_2: 4R_25_0.3 (1), 4R_25_0.6 (2), LED_25_2.C, SHIFT_25.2 (QC)
Q25_3: 4R_25_0.4 (1), 4R_25_0.5 (2), LED_25_3.C, SHIFT_25.3 (QD)
Q25_4: 4R_25_1.1, 4R_25_1.8 (2), LED_25_4.C, SHIFT_25.4 (QE)
Q25_5: 4R_25_1.2 (1), 4R_25_1.7 (2), LED_25_5.C, SHIFT_25.5 (QF)
Q25_6: 4R_25_1.3 (1), 4R_25_1.6 (2), LED_25_6.C, SHIFT_25.6 (QG)
Q25_7: 4R_25_1.4 (1), 4R_25_1.5 (2), LED_25_7.C, SHIFT_25.7 (QH)
Q26_0: 4R_26_0.1, 4R_26_0.8 (2), LED_26_0.C, SHIFT_26.15 (QA)
Q26_1: 4R_26_0.2 (1), 4R_26_0.7 (2), LED_26_1.C, SHIFT_26.1 (QB)
Q26_2: 4R_26_0.3 (1), 4R_26_0.6 (2), LED_26_2.C, SHIFT_26.2 (QC)
Q26_3: 4R_26_0.4 (1), 4R_26_0.5 (2), LED_26_3.C, SHIFT_26.3 (QD)
Q26_4: 4R_26_1.1, 4R_26_1.8 (2), LED_26_4.C, SHIFT_26.4 (QE)
Q26_5: 4R_26_1.2 (1), 4R_26_1.7 (2), LED_26_5.C, SHIFT_26.5 (QF)
Q26_6: 4R_26_1.3 (1), 4R_26_1.6 (2), LED_26_6.C, SHIFT_26.6 (QG)
Q26_7: 4R_26_1.4 (1), 4R_26_1.5 (2), LED_26_7.C, SHIFT_26.7 (QH)
Q27_0: 4R_27_0.1, 4R_27_0.8 (2), LED_27_0.C, SHIFT_27.15 (QA)
Q27_1: 4R_27_0.2 (1), 4R_27_0.7 (2), LED_27_1.C, SHIFT_27.1 (QB)
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
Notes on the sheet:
5V (MR)
11 (SH_CP)
12 (ST_CP)
13 (OE)
14 (DS)

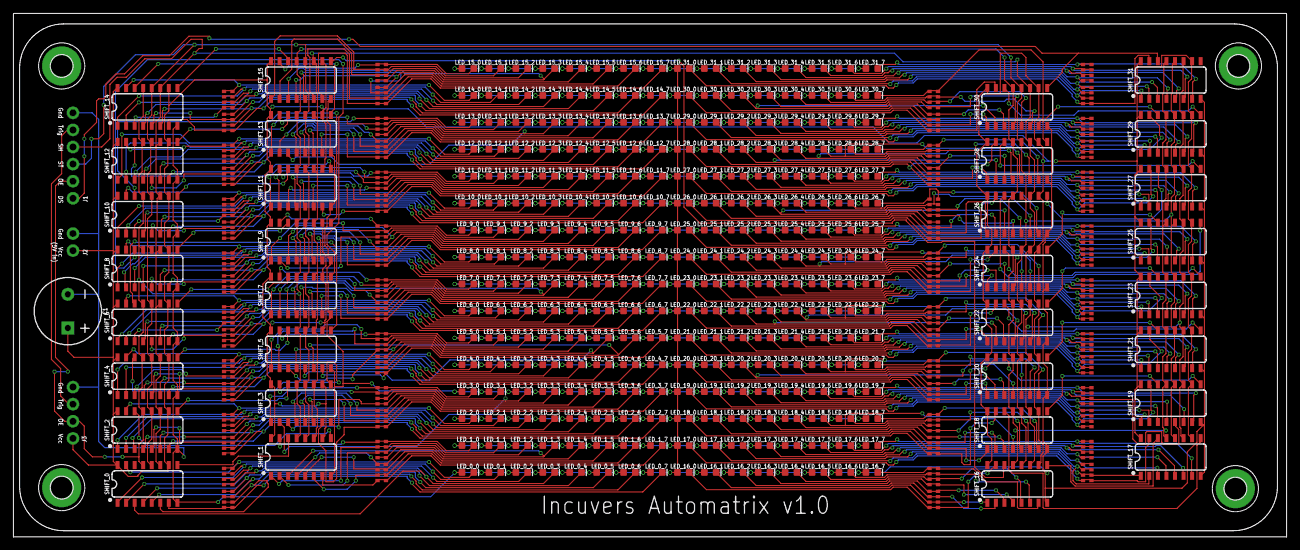
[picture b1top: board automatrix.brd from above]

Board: 2 copper layers, 189.1 x 77.7 mm, 360 parts (0 on the bottom side), 293 nets.

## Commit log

2019-04-05 init readme
2019-04-05 bank schematic
2019-04-05 populated with a rough design document
2019-04-05 fixed svg
2019-04-05 typos
2019-04-08 python model to turn on LEDs
2019-04-08 some minimalist tests
2019-04-24 LED location design
2019-05-06 Version 1.0 of the board

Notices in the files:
parts and their libraries:
SparkFun-LED: Licensing: Creative Commons ShareAlike 4.0 International - https://creativecommons.org/licenses/by-sa/4.0
